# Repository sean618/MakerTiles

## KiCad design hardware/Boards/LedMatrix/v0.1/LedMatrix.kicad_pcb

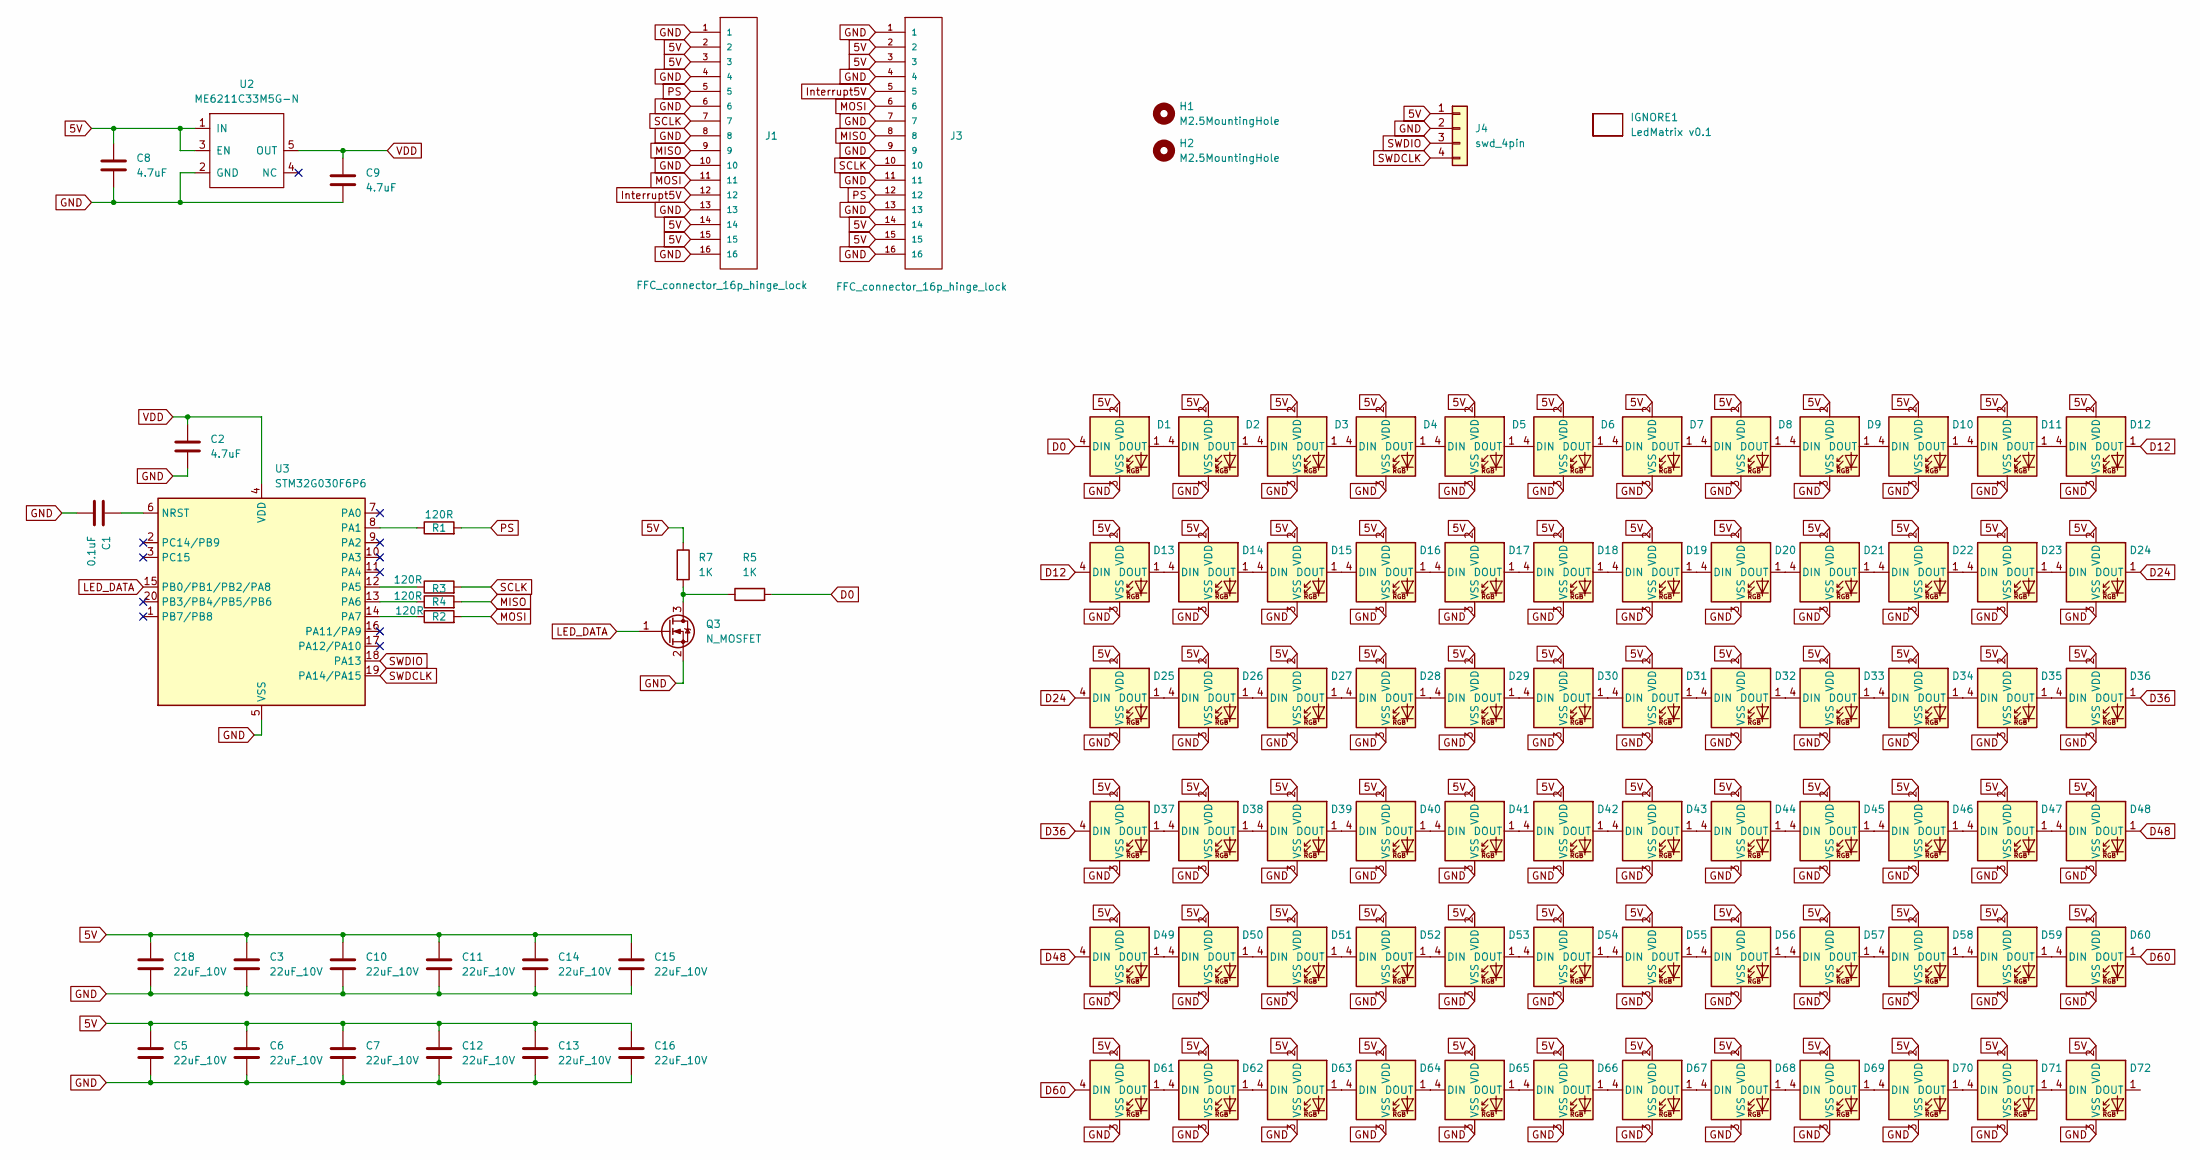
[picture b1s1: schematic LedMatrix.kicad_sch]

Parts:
C1: 0.1uF; C_0402_1005Metric
C2, C8, C9: 4.7uF; C_0402_1005Metric
C3, C5, C6, C7, C10, C11, C12, C13, C14, C15, C16, C18: 22uF_10V; C_0603_1608Metric
D1, D2, D3, D4, D5, D6, D7, D8, D9, D10, D11, D12, D13, D14, D15, D16, D17, D18, D19, D20, D21, D22, D23, D24, D25, D26, D27, D28, D29, D30, D31, D32, D33, D34, D35, D36, D37, D38, D39, D40, D41, D42, D43, D44, D45, D46, D47, D48, D49, D50, D51, D52, D53, D54, D55, D56, D57, D58, D59, D60, D61, D62, D63, D64, D65, D66, D67, D68, D69, D70, D71, D72: ws2812b_1615; WS2812B_1615
H1, H2: M2.5MountingHole; MountingHole_2.7mm_M2.5_ISO7380
IGNORE1: LedMatrix v0.1; BoardText
J1, J3: FFC_connector_16p_hinge_lock
J4: swd_4pin; swd_header
Q3: N_MOSFET; SOT-23
R1, R2, R3, R4: 120R; R_0402_1005Metric
R5, R7: 1K; R_0402_1005Metric
U2: ME6211C33M5G-N; SOT-23-5
U3: STM32G030F6P6; TSSOP-20_4.4x6.5mm_P0.65mm

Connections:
5V: C3.1, C5.1, C6.1, C7.1, C8.1, C10.1, C11.1, C12.1, C13.1, C14.1, C15.1, C16.1, C18.1, D1.2 (VDD), D2.2 (VDD), D3.2 (VDD), D4.2 (VDD), D5.2 (VDD), D6.2 (VDD), D7.2 (VDD), D8.2 (VDD), D9.2 (VDD), D10.2 (VDD), D11.2 (VDD), D12.2 (VDD), D13.2 (VDD), D14.2 (VDD), D15.2 (VDD), D16.2 (VDD), D17.2 (VDD), D18.2 (VDD), D19.2 (VDD), D20.2 (VDD), D21.2 (VDD), D22.2 (VDD), D23.2 (VDD), D24.2 (VDD), D25.2 (VDD), D26.2 (VDD), D27.2 (VDD), D28.2 (VDD), D29.2 (VDD), D30.2 (VDD), D31.2 (VDD), D32.2 (VDD), D33.2 (VDD), D34.2 (VDD), D35.2 (VDD), D36.2 (VDD), D37.2 (VDD), D38.2 (VDD), D39.2 (VDD), D40.2 (VDD), D41.2 (VDD), D42.2 (VDD), D43.2 (VDD), D44.2 (VDD), D45.2 (VDD), D46.2 (VDD), D47.2 (VDD), D48.2 (VDD), D49.2 (VDD), D50.2 (VDD), D51.2 (VDD), D52.2 (VDD), D53.2 (VDD), D54.2 (VDD), D55.2 (VDD), D56.2 (VDD), D57.2 (VDD), D58.2 (VDD), D59.2 (VDD), D60.2 (VDD), D61.2 (VDD), D62.2 (VDD), D63.2 (VDD), D64.2 (VDD), D65.2 (VDD), D66.2 (VDD), D67.2 (VDD), D68.2 (VDD), D69.2 (VDD), D70.2 (VDD), D71.2 (VDD), D72.2 (VDD), J1.2, J1.3, J1.14, J1.15, J3.2, J3.3, J3.14, J3.15, J4.1, R7.1, U2.1 (IN), U2.3 (EN)
D0: D1.4 (DIN), R5.2
D12: D12.1 (DOUT), D13.4 (DIN)
D24: D24.1 (DOUT), D25.4 (DIN)
D36: D36.1 (DOUT), D37.4 (DIN)
D48: D48.1 (DOUT), D49.4 (DIN)
D60: D60.1 (DOUT), D61.4 (DIN)
GND: C1.2, C2.2, C3.2, C5.2, C6.2, C7.2, C8.2, C9.2, C10.2, C11.2, C12.2, C13.2, C14.2, C15.2, C16.2, C18.2, D1.3 (VSS), D2.3 (VSS), D3.3 (VSS), D4.3 (VSS), D5.3 (VSS), D6.3 (VSS), D7.3 (VSS), D8.3 (VSS), D9.3 (VSS), D10.3 (VSS), D11.3 (VSS), D12.3 (VSS), D13.3 (VSS), D14.3 (VSS), D15.3 (VSS), D16.3 (VSS), D17.3 (VSS), D18.3 (VSS), D19.3 (VSS), D20.3 (VSS), D21.3 (VSS), D22.3 (VSS), D23.3 (VSS), D24.3 (VSS), D25.3 (VSS), D26.3 (VSS), D27.3 (VSS), D28.3 (VSS), D29.3 (VSS), D30.3 (VSS), D31.3 (VSS), D32.3 (VSS), D33.3 (VSS), D34.3 (VSS), D35.3 (VSS), D36.3 (VSS), D37.3 (VSS), D38.3 (VSS), D39.3 (VSS), D40.3 (VSS), D41.3 (VSS), D42.3 (VSS), D43.3 (VSS), D44.3 (VSS), D45.3 (VSS), D46.3 (VSS), D47.3 (VSS), D48.3 (VSS), D49.3 (VSS), D50.3 (VSS), D51.3 (VSS), D52.3 (VSS), D53.3 (VSS), D54.3 (VSS), D55.3 (VSS), D56.3 (VSS), D57.3 (VSS), D58.3 (VSS), D59.3 (VSS), D60.3 (VSS), D61.3 (VSS), D62.3 (VSS), D63.3 (VSS), D64.3 (VSS), D65.3 (VSS), D66.3 (VSS), D67.3 (VSS), D68.3 (VSS), D69.3 (VSS), D70.3 (VSS), D71.3 (VSS), D72.3 (VSS), J1.1, J1.4, J1.6, J1.8, J1.10, J1.13, J1.16, J3.1, J3.4, J3.7, J3.9, J3.11, J3.13, J3.16, J4.2, Q3.2 (S), U2.2 (GND), U3.5 (VSS)
Interrupt5V: J1.12, J3.5
LED_DATA: Q3.1 (G), U3.15 (PB0/PB1/PB2/PA8)
MISO: J1.9, J3.8, R4.2
MOSI: J1.11, J3.6, R2.2
unnamed: D1.1 (DOUT), D2.4 (DIN)
unnamed: D2.1 (DOUT), D3.4 (DIN)
unnamed: D3.1 (DOUT), D4.4 (DIN)
unnamed: D4.1 (DOUT), D5.4 (DIN)
unnamed: D5.1 (DOUT), D6.4 (DIN)
unnamed: D6.1 (DOUT), D7.4 (DIN)
unnamed: D7.1 (DOUT), D8.4 (DIN)
unnamed: D8.1 (DOUT), D9.4 (DIN)
unnamed: D9.1 (DOUT), D10.4 (DIN)
unnamed: D10.1 (DOUT), D11.4 (DIN)
unnamed: D11.1 (DOUT), D12.4 (DIN)
unnamed: D13.1 (DOUT), D14.4 (DIN)
unnamed: D14.1 (DOUT), D15.4 (DIN)
unnamed: D15.1 (DOUT), D16.4 (DIN)
unnamed: D16.1 (DOUT), D17.4 (DIN)
unnamed: D17.1 (DOUT), D18.4 (DIN)
unnamed: D18.1 (DOUT), D19.4 (DIN)
unnamed: D19.1 (DOUT), D20.4 (DIN)
unnamed: D20.1 (DOUT), D21.4 (DIN)
unnamed: D21.1 (DOUT), D22.4 (DIN)
unnamed: D22.1 (DOUT), D23.4 (DIN)
unnamed: D23.1 (DOUT), D24.4 (DIN)
unnamed: D25.1 (DOUT), D26.4 (DIN)
unnamed: D26.1 (DOUT), D27.4 (DIN)
unnamed: D27.1 (DOUT), D28.4 (DIN)
unnamed: D28.1 (DOUT), D29.4 (DIN)
unnamed: D29.1 (DOUT), D30.4 (DIN)
unnamed: D30.1 (DOUT), D31.4 (DIN)
unnamed: D31.1 (DOUT), D32.4 (DIN)
unnamed: D32.1 (DOUT), D33.4 (DIN)
unnamed: D33.1 (DOUT), D34.4 (DIN)
unnamed: D34.1 (DOUT), D35.4 (DIN)
unnamed: D35.1 (DOUT), D36.4 (DIN)
unnamed: D37.1 (DOUT), D38.4 (DIN)
unnamed: D38.1 (DOUT), D39.4 (DIN)
unnamed: D39.1 (DOUT), D40.4 (DIN)
unnamed: D40.1 (DOUT), D41.4 (DIN)
unnamed: D41.1 (DOUT), D42.4 (DIN)
unnamed: D42.1 (DOUT), D43.4 (DIN)
unnamed: D43.1 (DOUT), D44.4 (DIN)
unnamed: D44.1 (DOUT), D45.4 (DIN)
unnamed: D45.1 (DOUT), D46.4 (DIN)
unnamed: D46.1 (DOUT), D47.4 (DIN)
unnamed: D47.1 (DOUT), D48.4 (DIN)
unnamed: D49.1 (DOUT), D50.4 (DIN)
unnamed: D50.1 (DOUT), D51.4 (DIN)
unnamed: D51.1 (DOUT), D52.4 (DIN)
unnamed: D52.1 (DOUT), D53.4 (DIN)
unnamed: D53.1 (DOUT), D54.4 (DIN)
unnamed: D54.1 (DOUT), D55.4 (DIN)
unnamed: D55.1 (DOUT), D56.4 (DIN)
unnamed: D56.1 (DOUT), D57.4 (DIN)
unnamed: D57.1 (DOUT), D58.4 (DIN)
unnamed: D58.1 (DOUT), D59.4 (DIN)
unnamed: D59.1 (DOUT), D60.4 (DIN)
unnamed: D61.1 (DOUT), D62.4 (DIN)
unnamed: D62.1 (DOUT), D63.4 (DIN)
unnamed: D63.1 (DOUT), D64.4 (DIN)
unnamed: D64.1 (DOUT), D65.4 (DIN)
unnamed: D65.1 (DOUT), D66.4 (DIN)
unnamed: D66.1 (DOUT), D67.4 (DIN)
unnamed: D67.1 (DOUT), D68.4 (DIN)
unnamed: D68.1 (DOUT), D69.4 (DIN)
unnamed: D69.1 (DOUT), D70.4 (DIN)
unnamed: D70.1 (DOUT), D71.4 (DIN)
unnamed: D71.1 (DOUT), D72.4 (DIN)
unnamed: Q3.3 (D), R5.1, R7.2
unnamed: C1.1, U3.6 (NRST)
unnamed: R1.1, U3.8 (PA1)
unnamed: R3.1, U3.12 (PA5)
unnamed: R4.1, U3.13 (PA6)
unnamed: R2.1, U3.14 (PA7)
PS: J1.5, J3.12, R1.2
SCLK: J1.7, J3.10, R3.2
SWDCLK: J4.4, U3.19 (PA14/PA15)
SWDIO: J4.3, U3.18 (PA13)
VDD: C2.1, C9.1, U2.5 (OUT), U3.4 (VDD)

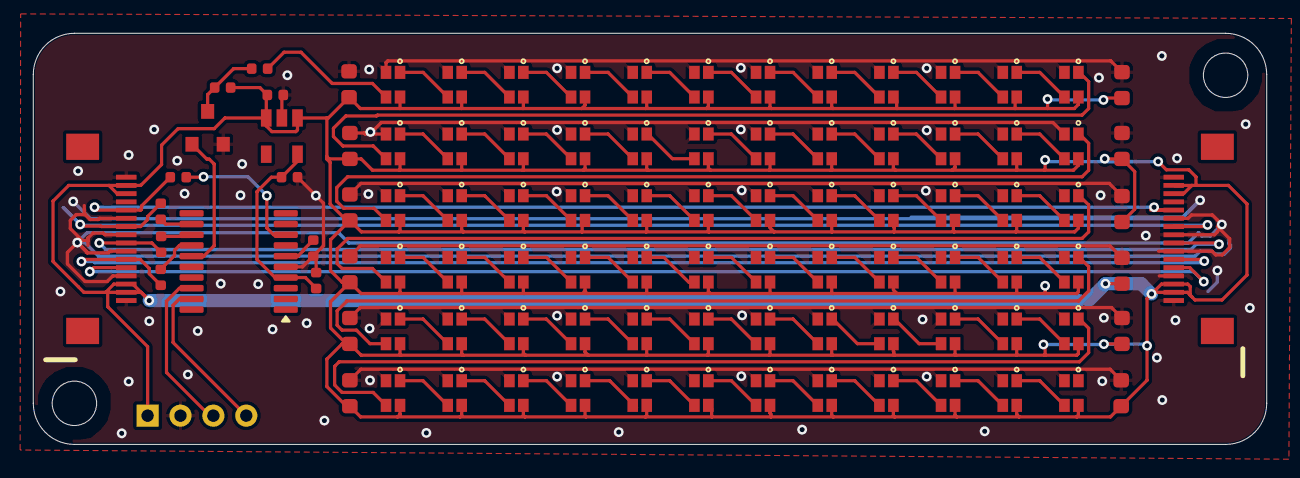
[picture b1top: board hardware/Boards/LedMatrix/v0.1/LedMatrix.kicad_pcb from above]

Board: 4 copper layers, 75.0 x 25.0 mm, 103 parts (0 on the bottom side), 89 nets.

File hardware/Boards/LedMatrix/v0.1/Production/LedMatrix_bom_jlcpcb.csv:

Comment,Designator,Footprint,LCSC Part Number
4.7uF,"C9,C8,C2",C_0402_1005Metric,C23733
ws2812b_1615,"D34,D5,D32,D6,D67,D49,D54,D58,D9,D72,D13,D50,D53,D33,D47,D48,D17,D57,D29,D22,D70,D60,D26,D41,D14,D31,D10,D68,D38,D35,D36,D7,D24,D71,D37,D1,D64,D23,D19,D69,D2,D45,D20,D18,D66,D44,D39,D52,D28,D42,D61,D65,D8,D63,D59,D46,D55,D30,D56,D25,D21,D51,D4,D11,D16,D27,D15,D40,D43,D12,D62,D3",WS2812B_1615,C5349954
FFC_connector_16p_hinge_lock,"J1,J3",FFC_connector_16p_hinge_lock,C262665
1K,"R7,R5",R_0402_1005Metric,C11702
22uF_10V,"C7,C6,C15,C5,C10,C12,C14,C13,C18,C11,C3,C16",C_0603_1608Metric,C86295
ME6211C33M5G-N,U2,SOT-23-5,C81233
120R,"R2,R3,R4,R1",R_0402_1005Metric,C25079
STM32G030F6P6,U3,TSSOP-20_4.4x6.5mm_P0.65mm,C529330
N_MOSFET,Q3,SOT-23,C8545
0.1uF,C1,C_0402_1005Metric,C1525

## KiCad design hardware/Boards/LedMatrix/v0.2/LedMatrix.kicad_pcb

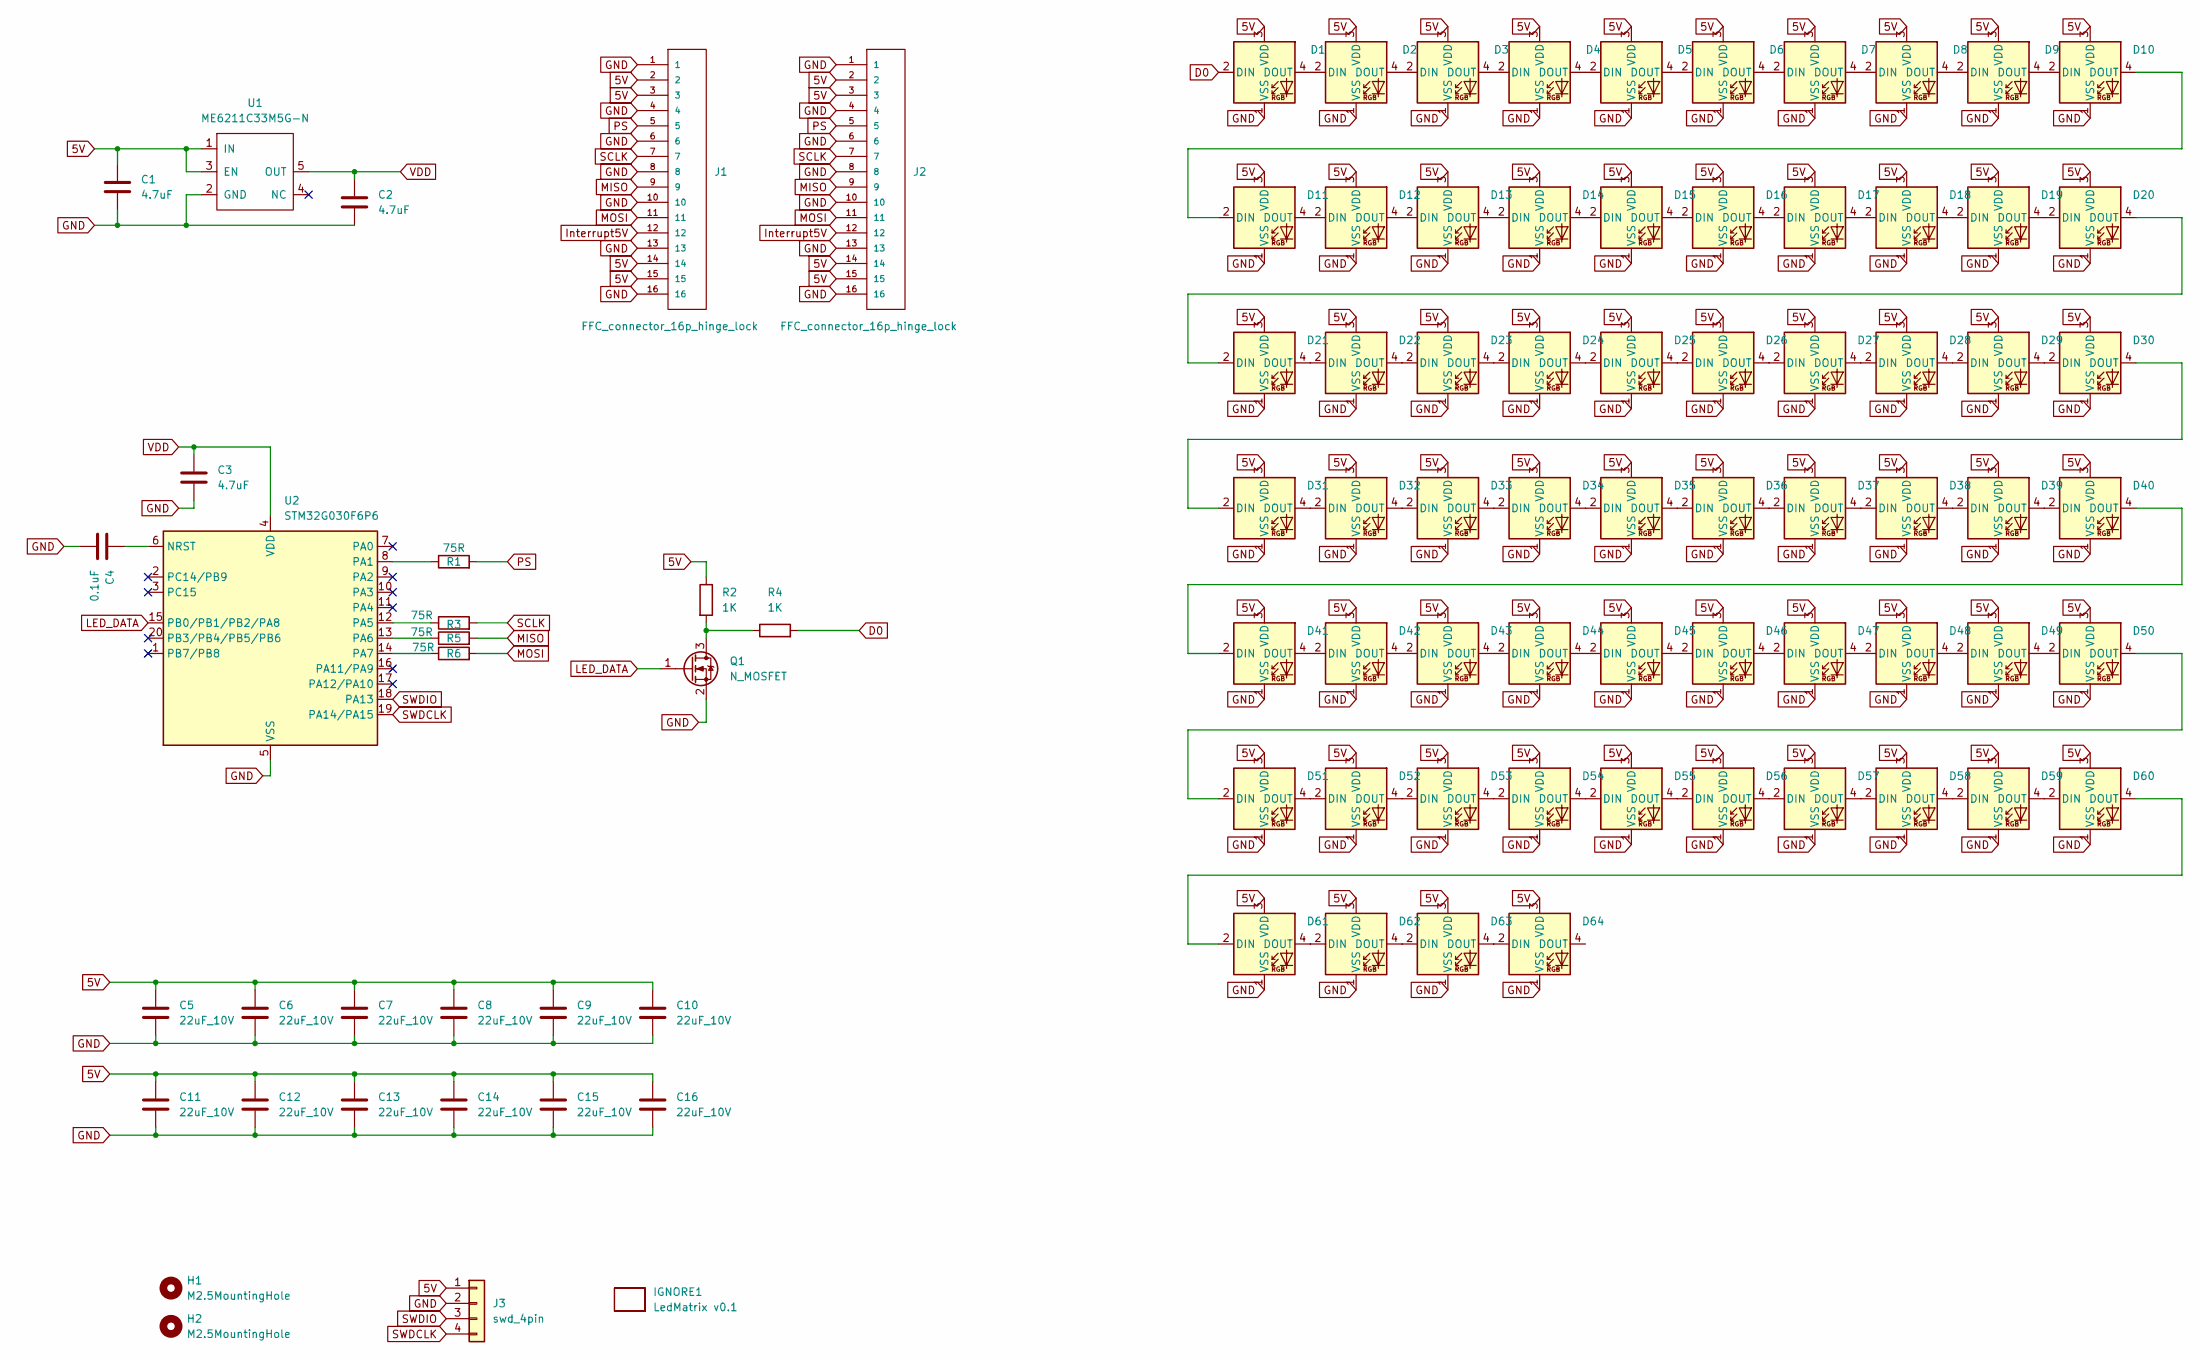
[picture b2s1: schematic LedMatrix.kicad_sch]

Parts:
C1, C2, C3: 4.7uF; C_0402_1005Metric
C4: 0.1uF; C_0402_1005Metric
C5, C6, C7, C8, C9, C10, C11, C12, C13, C14, C15, C16: 22uF_10V; C_0603_1608Metric
D1, D2, D3, D4, D5, D6, D7, D8, D9, D10, D11, D12, D13, D14, D15, D16, D17, D18, D19, D20, D21, D22, D23, D24, D25, D26, D27, D28, D29, D30, D31, D32, D33, D34, D35, D36, D37, D38, D39, D40, D41, D42, D43, D44, D45, D46, D47, D48, D49, D50, D51, D52, D53, D54, D55, D56, D57, D58, D59, D60, D61, D62, D63, D64: xl_ws2812b_small
H1, H2: M2.5MountingHole; MountingHole_2.7mm_M2.5_ISO7380
IGNORE1: LedMatrix v0.1; BoardText
J1, J2: FFC_connector_16p_hinge_lock
J3: swd_4pin; swd_header
Q1: N_MOSFET; SOT-23
R1, R3, R5, R6: 75R; R_0402_1005Metric
R2, R4: 1K; R_0402_1005Metric
U1: ME6211C33M5G-N; SOT-23-5
U2: STM32G030F6P6; TSSOP-20_4.4x6.5mm_P0.65mm

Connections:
5V: C1.1, C5.1, C6.1, C7.1, C8.1, C9.1, C10.1, C11.1, C12.1, C13.1, C14.1, C15.1, C16.1, D1.3 (VDD), D2.3 (VDD), D3.3 (VDD), D4.3 (VDD), D5.3 (VDD), D6.3 (VDD), D7.3 (VDD), D8.3 (VDD), D9.3 (VDD), D10.3 (VDD), D11.3 (VDD), D12.3 (VDD), D13.3 (VDD), D14.3 (VDD), D15.3 (VDD), D16.3 (VDD), D17.3 (VDD), D18.3 (VDD), D19.3 (VDD), D20.3 (VDD), D21.3 (VDD), D22.3 (VDD), D23.3 (VDD), D24.3 (VDD), D25.3 (VDD), D26.3 (VDD), D27.3 (VDD), D28.3 (VDD), D29.3 (VDD), D30.3 (VDD), D31.3 (VDD), D32.3 (VDD), D33.3 (VDD), D34.3 (VDD), D35.3 (VDD), D36.3 (VDD), D37.3 (VDD), D38.3 (VDD), D39.3 (VDD), D40.3 (VDD), D41.3 (VDD), D42.3 (VDD), D43.3 (VDD), D44.3 (VDD), D45.3 (VDD), D46.3 (VDD), D47.3 (VDD), D48.3 (VDD), D49.3 (VDD), D50.3 (VDD), D51.3 (VDD), D52.3 (VDD), D53.3 (VDD), D54.3 (VDD), D55.3 (VDD), D56.3 (VDD), D57.3 (VDD), D58.3 (VDD), D59.3 (VDD), D60.3 (VDD), D61.3 (VDD), D62.3 (VDD), D63.3 (VDD), D64.3 (VDD), J1.2, J1.3, J1.14, J1.15, J2.2, J2.3, J2.14, J2.15, J3.1, R2.1, U1.1 (IN), U1.3 (EN)
D0: D1.2 (DIN), R4.2
GND: C1.2, C2.2, C3.2, C4.2, C5.2, C6.2, C7.2, C8.2, C9.2, C10.2, C11.2, C12.2, C13.2, C14.2, C15.2, C16.2, D1.1 (VSS), D2.1 (VSS), D3.1 (VSS), D4.1 (VSS), D5.1 (VSS), D6.1 (VSS), D7.1 (VSS), D8.1 (VSS), D9.1 (VSS), D10.1 (VSS), D11.1 (VSS), D12.1 (VSS), D13.1 (VSS), D14.1 (VSS), D15.1 (VSS), D16.1 (VSS), D17.1 (VSS), D18.1 (VSS), D19.1 (VSS), D20.1 (VSS), D21.1 (VSS), D22.1 (VSS), D23.1 (VSS), D24.1 (VSS), D25.1 (VSS), D26.1 (VSS), D27.1 (VSS), D28.1 (VSS), D29.1 (VSS), D30.1 (VSS), D31.1 (VSS), D32.1 (VSS), D33.1 (VSS), D34.1 (VSS), D35.1 (VSS), D36.1 (VSS), D37.1 (VSS), D38.1 (VSS), D39.1 (VSS), D40.1 (VSS), D41.1 (VSS), D42.1 (VSS), D43.1 (VSS), D44.1 (VSS), D45.1 (VSS), D46.1 (VSS), D47.1 (VSS), D48.1 (VSS), D49.1 (VSS), D50.1 (VSS), D51.1 (VSS), D52.1 (VSS), D53.1 (VSS), D54.1 (VSS), D55.1 (VSS), D56.1 (VSS), D57.1 (VSS), D58.1 (VSS), D59.1 (VSS), D60.1 (VSS), D61.1 (VSS), D62.1 (VSS), D63.1 (VSS), D64.1 (VSS), J1.1, J1.4, J1.6, J1.8, J1.10, J1.13, J1.16, J2.1, J2.4, J2.6, J2.8, J2.10, J2.13, J2.16, J3.2, Q1.2 (S), U1.2 (GND), U2.5 (VSS)
Interrupt5V: J1.12, J2.12
LED_DATA: Q1.1 (G), U2.15 (PB0/PB1/PB2/PA8)
MISO: J1.9, J2.9, R5.2
MOSI: J1.11, J2.11, R6.2
unnamed: D1.4 (DOUT), D2.2 (DIN)
unnamed: D2.4 (DOUT), D3.2 (DIN)
unnamed: D3.4 (DOUT), D4.2 (DIN)
unnamed: D4.4 (DOUT), D5.2 (DIN)
unnamed: D5.4 (DOUT), D6.2 (DIN)
unnamed: D6.4 (DOUT), D7.2 (DIN)
unnamed: D7.4 (DOUT), D8.2 (DIN)
unnamed: D8.4 (DOUT), D9.2 (DIN)
unnamed: D9.4 (DOUT), D10.2 (DIN)
unnamed: D10.4 (DOUT), D11.2 (DIN)
unnamed: D11.4 (DOUT), D12.2 (DIN)
unnamed: D12.4 (DOUT), D13.2 (DIN)
unnamed: D13.4 (DOUT), D14.2 (DIN)
unnamed: D14.4 (DOUT), D15.2 (DIN)
unnamed: D15.4 (DOUT), D16.2 (DIN)
unnamed: D16.4 (DOUT), D17.2 (DIN)
unnamed: D17.4 (DOUT), D18.2 (DIN)
unnamed: D18.4 (DOUT), D19.2 (DIN)
unnamed: D19.4 (DOUT), D20.2 (DIN)
unnamed: D20.4 (DOUT), D21.2 (DIN)
unnamed: D21.4 (DOUT), D22.2 (DIN)
unnamed: D22.4 (DOUT), D23.2 (DIN)
unnamed: D23.4 (DOUT), D24.2 (DIN)
unnamed: D24.4 (DOUT), D25.2 (DIN)
unnamed: D25.4 (DOUT), D26.2 (DIN)
unnamed: D26.4 (DOUT), D27.2 (DIN)
unnamed: D27.4 (DOUT), D28.2 (DIN)
unnamed: D28.4 (DOUT), D29.2 (DIN)
unnamed: D29.4 (DOUT), D30.2 (DIN)
unnamed: D30.4 (DOUT), D31.2 (DIN)
unnamed: D31.4 (DOUT), D32.2 (DIN)
unnamed: D32.4 (DOUT), D33.2 (DIN)
unnamed: D33.4 (DOUT), D34.2 (DIN)
unnamed: D34.4 (DOUT), D35.2 (DIN)
unnamed: D35.4 (DOUT), D36.2 (DIN)
unnamed: D36.4 (DOUT), D37.2 (DIN)
unnamed: D37.4 (DOUT), D38.2 (DIN)
unnamed: D38.4 (DOUT), D39.2 (DIN)
unnamed: D39.4 (DOUT), D40.2 (DIN)
unnamed: D40.4 (DOUT), D41.2 (DIN)
unnamed: D41.4 (DOUT), D42.2 (DIN)
unnamed: D42.4 (DOUT), D43.2 (DIN)
unnamed: D43.4 (DOUT), D44.2 (DIN)
unnamed: D44.4 (DOUT), D45.2 (DIN)
unnamed: D45.4 (DOUT), D46.2 (DIN)
unnamed: D46.4 (DOUT), D47.2 (DIN)
unnamed: D47.4 (DOUT), D48.2 (DIN)
unnamed: D48.4 (DOUT), D49.2 (DIN)
unnamed: D49.4 (DOUT), D50.2 (DIN)
unnamed: D50.4 (DOUT), D51.2 (DIN)
unnamed: D51.4 (DOUT), D52.2 (DIN)
unnamed: D52.4 (DOUT), D53.2 (DIN)
unnamed: D53.4 (DOUT), D54.2 (DIN)
unnamed: D54.4 (DOUT), D55.2 (DIN)
unnamed: D55.4 (DOUT), D56.2 (DIN)
unnamed: D56.4 (DOUT), D57.2 (DIN)
unnamed: D57.4 (DOUT), D58.2 (DIN)
unnamed: D58.4 (DOUT), D59.2 (DIN)
unnamed: D59.4 (DOUT), D60.2 (DIN)
unnamed: D60.4 (DOUT), D61.2 (DIN)
unnamed: D61.4 (DOUT), D62.2 (DIN)
unnamed: D62.4 (DOUT), D63.2 (DIN)
unnamed: D63.4 (DOUT), D64.2 (DIN)
unnamed: Q1.3 (D), R2.2, R4.1
unnamed: C4.1, U2.6 (NRST)
unnamed: R1.1, U2.8 (PA1)
unnamed: R3.1, U2.12 (PA5)
unnamed: R5.1, U2.13 (PA6)
unnamed: R6.1, U2.14 (PA7)
PS: J1.5, J2.5, R1.2
SCLK: J1.7, J2.7, R3.2
SWDCLK: J3.4, U2.19 (PA14/PA15)
SWDIO: J3.3, U2.18 (PA13)
VDD: C2.1, C3.1, U1.5 (OUT), U2.4 (VDD)

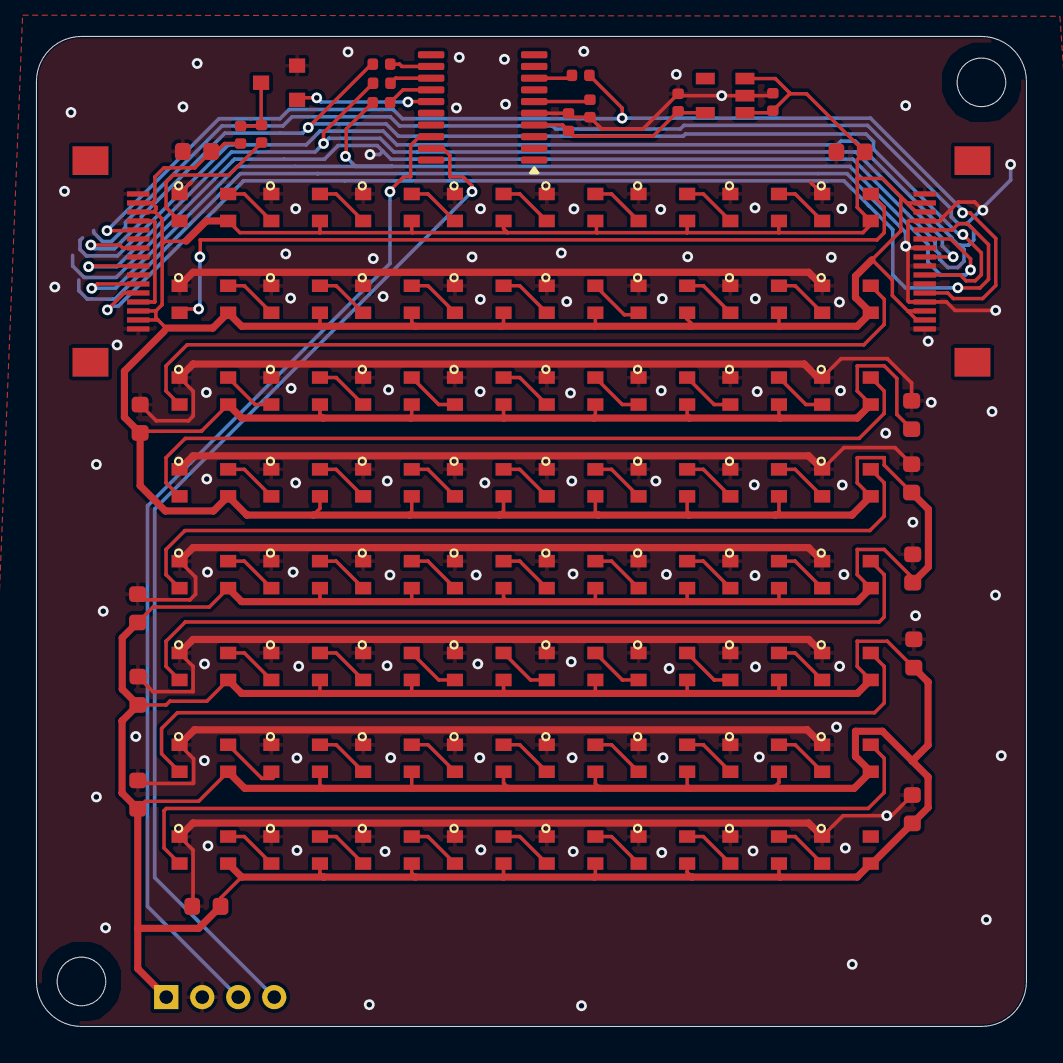
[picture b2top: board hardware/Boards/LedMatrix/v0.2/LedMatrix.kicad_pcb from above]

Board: 4 copper layers, 55.0 x 55.0 mm, 95 parts (0 on the bottom side), 81 nets.

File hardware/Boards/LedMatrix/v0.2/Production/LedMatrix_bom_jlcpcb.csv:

Comment,Designator,Footprint,LCSC Part Number
22uF_10V,"C11,C16,C12,C6,C5,C9,C15,C13,C8,C10,C7,C14",C_0603_1608Metric,C86295
xl_ws2812b_small,"D22,D51,D1,D25,D12,D63,D54,D59,D32,D8,D21,D64,D43,D57,D40,D49,D11,D6,D3,D39,D29,D36,D14,D5,D34,D30,D24,D4,D17,D47,D37,D19,D15,D20,D41,D2,D18,D31,D38,D62,D44,D13,D35,D26,D50,D52,D53,D9,D55,D48,D61,D46,D45,D10,D23,D58,D27,D56,D42,D16,D7,D28,D33,D60",xl_ws2812b_small,C2890364
1K,"R2,R4",R_0402_1005Metric,C11702
FFC_connector_16p_hinge_lock,"J1,J2",FFC_connector_16p_hinge_lock,C262665
4.7uF,"C1,C2,C3",C_0402_1005Metric,C23733
75R,"R3,R1,R6,R5",R_0402_1005Metric,C25133
0.1uF,C4,C_0402_1005Metric,C1525
STM32G030F6P6,U2,TSSOP-20_4.4x6.5mm_P0.65mm,C529330
ME6211C33M5G-N,U1,SOT-23-5,C81233
N_MOSFET,Q1,SOT-23,C8545

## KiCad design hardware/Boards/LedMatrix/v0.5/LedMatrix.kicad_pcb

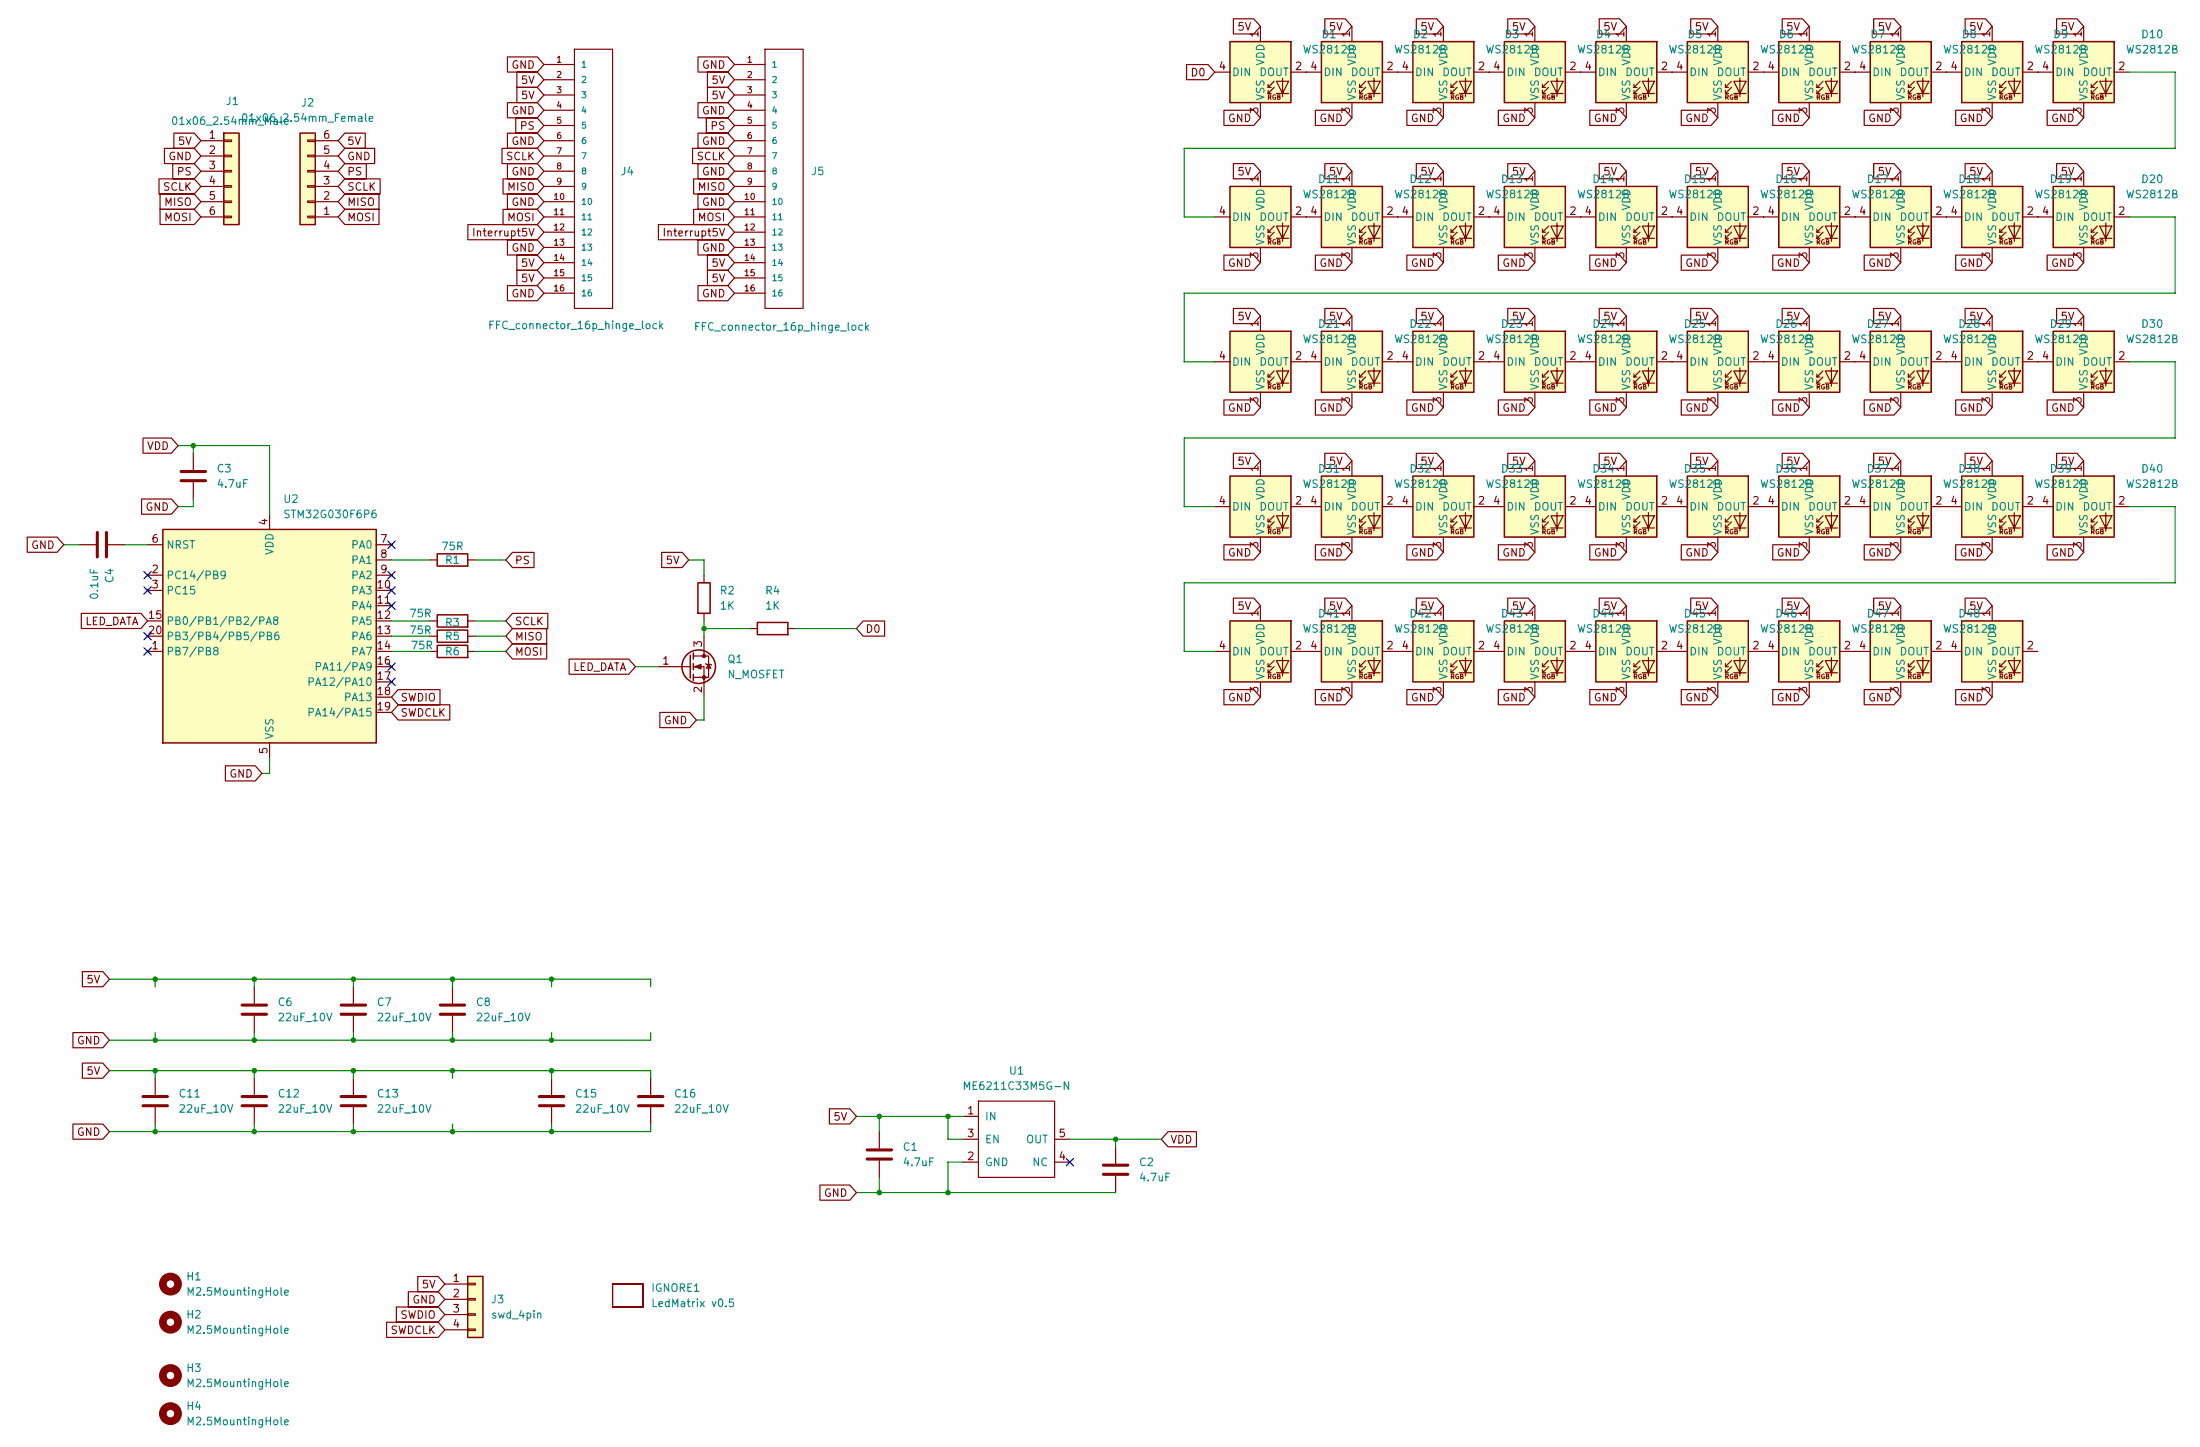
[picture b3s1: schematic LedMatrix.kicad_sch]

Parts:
C1, C2, C3: 4.7uF; C_0402_1005Metric
C4: 0.1uF; C_0402_1005Metric
C6, C7, C8, C11, C12, C13, C15, C16: 22uF_10V; C_0603_1608Metric
D1, D2, D3, D4, D5, D6, D7, D8, D9, D10, D11, D12, D13, D14, D15, D16, D17, D18, D19, D20, D21, D22, D23, D24, D25, D26, D27, D28, D29, D30, D31, D32, D33, D34, D35, D36, D37, D38, D39, D40, D41, D42, D43, D44, D45, D46, D47, D48, D49: WS2812B; LED_WS2812B_PLCC4_5.0x5.0mm_P3.2mm
H1, H2, H3, H4: M2.5MountingHole; MountingHole_2.7mm_M2.5_ISO7380
IGNORE1: LedMatrix v0.5; BoardText
J1: 01x06_2.54mm_Male
J2: 01x06_2.54mm_Female
J3: swd_4pin; swd_header
J4, J5: FFC_connector_16p_hinge_lock
Q1: N_MOSFET; SOT-23
R1, R3, R5, R6: 75R; R_0402_1005Metric
R2, R4: 1K; R_0402_1005Metric
U1: ME6211C33M5G-N; SOT-23-5
U2: STM32G030F6P6; TSSOP-20_4.4x6.5mm_P0.65mm

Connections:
5V: C1.1, C6.1, C7.1, C8.1, C11.1, C12.1, C13.1, C15.1, C16.1, D1.1 (VDD), D2.1 (VDD), D3.1 (VDD), D4.1 (VDD), D5.1 (VDD), D6.1 (VDD), D7.1 (VDD), D8.1 (VDD), D9.1 (VDD), D10.1 (VDD), D11.1 (VDD), D12.1 (VDD), D13.1 (VDD), D14.1 (VDD), D15.1 (VDD), D16.1 (VDD), D17.1 (VDD), D18.1 (VDD), D19.1 (VDD), D20.1 (VDD), D21.1 (VDD), D22.1 (VDD), D23.1 (VDD), D24.1 (VDD), D25.1 (VDD), D26.1 (VDD), D27.1 (VDD), D28.1 (VDD), D29.1 (VDD), D30.1 (VDD), D31.1 (VDD), D32.1 (VDD), D33.1 (VDD), D34.1 (VDD), D35.1 (VDD), D36.1 (VDD), D37.1 (VDD), D38.1 (VDD), D39.1 (VDD), D40.1 (VDD), D41.1 (VDD), D42.1 (VDD), D43.1 (VDD), D44.1 (VDD), D45.1 (VDD), D46.1 (VDD), D47.1 (VDD), D48.1 (VDD), D49.1 (VDD), J1.1, J2.6, J3.1, J4.2, J4.3, J4.14, J4.15, J5.2, J5.3, J5.14, J5.15, R2.1, U1.1 (IN), U1.3 (EN)
D0: D1.4 (DIN), R4.2
GND: C1.2, C2.2, C3.2, C4.2, C6.2, C7.2, C8.2, C11.2, C12.2, C13.2, C15.2, C16.2, D1.3 (VSS), D2.3 (VSS), D3.3 (VSS), D4.3 (VSS), D5.3 (VSS), D6.3 (VSS), D7.3 (VSS), D8.3 (VSS), D9.3 (VSS), D10.3 (VSS), D11.3 (VSS), D12.3 (VSS), D13.3 (VSS), D14.3 (VSS), D15.3 (VSS), D16.3 (VSS), D17.3 (VSS), D18.3 (VSS), D19.3 (VSS), D20.3 (VSS), D21.3 (VSS), D22.3 (VSS), D23.3 (VSS), D24.3 (VSS), D25.3 (VSS), D26.3 (VSS), D27.3 (VSS), D28.3 (VSS), D29.3 (VSS), D30.3 (VSS), D31.3 (VSS), D32.3 (VSS), D33.3 (VSS), D34.3 (VSS), D35.3 (VSS), D36.3 (VSS), D37.3 (VSS), D38.3 (VSS), D39.3 (VSS), D40.3 (VSS), D41.3 (VSS), D42.3 (VSS), D43.3 (VSS), D44.3 (VSS), D45.3 (VSS), D46.3 (VSS), D47.3 (VSS), D48.3 (VSS), D49.3 (VSS), J1.2, J2.5, J3.2, J4.1, J4.4, J4.6, J4.8, J4.10, J4.13, J4.16, J5.1, J5.4, J5.6, J5.8, J5.10, J5.13, J5.16, Q1.2 (S), U1.2 (GND), U2.5 (VSS)
Interrupt5V: J4.12, J5.12
LED_DATA: Q1.1 (G), U2.15 (PB0/PB1/PB2/PA8)
MISO: J1.5, J2.2, J4.9, J5.9, R5.2
MOSI: J1.6, J2.1, J4.11, J5.11, R6.2
unnamed: D1.2 (DOUT), D2.4 (DIN)
unnamed: D2.2 (DOUT), D3.4 (DIN)
unnamed: D3.2 (DOUT), D4.4 (DIN)
unnamed: D4.2 (DOUT), D5.4 (DIN)
unnamed: D5.2 (DOUT), D6.4 (DIN)
unnamed: D6.2 (DOUT), D7.4 (DIN)
unnamed: D7.2 (DOUT), D8.4 (DIN)
unnamed: D8.2 (DOUT), D9.4 (DIN)
unnamed: D9.2 (DOUT), D10.4 (DIN)
unnamed: D10.2 (DOUT), D11.4 (DIN)
unnamed: D11.2 (DOUT), D12.4 (DIN)
unnamed: D12.2 (DOUT), D13.4 (DIN)
unnamed: D13.2 (DOUT), D14.4 (DIN)
unnamed: D14.2 (DOUT), D15.4 (DIN)
unnamed: D15.2 (DOUT), D16.4 (DIN)
unnamed: D16.2 (DOUT), D17.4 (DIN)
unnamed: D17.2 (DOUT), D18.4 (DIN)
unnamed: D18.2 (DOUT), D19.4 (DIN)
unnamed: D19.2 (DOUT), D20.4 (DIN)
unnamed: D20.2 (DOUT), D21.4 (DIN)
unnamed: D21.2 (DOUT), D22.4 (DIN)
unnamed: D22.2 (DOUT), D23.4 (DIN)
unnamed: D23.2 (DOUT), D24.4 (DIN)
unnamed: D24.2 (DOUT), D25.4 (DIN)
unnamed: D25.2 (DOUT), D26.4 (DIN)
unnamed: D26.2 (DOUT), D27.4 (DIN)
unnamed: D27.2 (DOUT), D28.4 (DIN)
unnamed: D28.2 (DOUT), D29.4 (DIN)
unnamed: D29.2 (DOUT), D30.4 (DIN)
unnamed: D30.2 (DOUT), D31.4 (DIN)
unnamed: D31.2 (DOUT), D32.4 (DIN)
unnamed: D32.2 (DOUT), D33.4 (DIN)
unnamed: D33.2 (DOUT), D34.4 (DIN)
unnamed: D34.2 (DOUT), D35.4 (DIN)
unnamed: D35.2 (DOUT), D36.4 (DIN)
unnamed: D36.2 (DOUT), D37.4 (DIN)
unnamed: D37.2 (DOUT), D38.4 (DIN)
unnamed: D38.2 (DOUT), D39.4 (DIN)
unnamed: D39.2 (DOUT), D40.4 (DIN)
unnamed: D40.2 (DOUT), D41.4 (DIN)
unnamed: D41.2 (DOUT), D42.4 (DIN)
unnamed: D42.2 (DOUT), D43.4 (DIN)
unnamed: D43.2 (DOUT), D44.4 (DIN)
unnamed: D44.2 (DOUT), D45.4 (DIN)
unnamed: D45.2 (DOUT), D46.4 (DIN)
unnamed: D46.2 (DOUT), D47.4 (DIN)
unnamed: D47.2 (DOUT), D48.4 (DIN)
unnamed: D48.2 (DOUT), D49.4 (DIN)
unnamed: Q1.3 (D), R2.2, R4.1
unnamed: C4.1, U2.6 (NRST)
unnamed: R1.1, U2.8 (PA1)
unnamed: R3.1, U2.12 (PA5)
unnamed: R5.1, U2.13 (PA6)
unnamed: R6.1, U2.14 (PA7)
PS: J1.3, J2.4, J4.5, J5.5, R1.2
SCLK: J1.4, J2.3, J4.7, J5.7, R3.2
SWDCLK: J3.4, U2.19 (PA14/PA15)
SWDIO: J3.3, U2.18 (PA13)
VDD: C2.1, C3.1, U1.5 (OUT), U2.4 (VDD)
